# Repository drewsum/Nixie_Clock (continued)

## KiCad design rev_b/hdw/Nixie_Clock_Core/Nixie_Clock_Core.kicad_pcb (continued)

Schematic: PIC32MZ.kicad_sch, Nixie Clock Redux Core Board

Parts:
R1001, R1002: 10k; R_0603; Tolerance 1%; Digi-Key PN 541-10.0KHCT-ND
U1001: PIC32MZ2048EFG100_IPF; TQFP-100_14x14mm_Pitch0.5mm; Digi-Key PN PIC32MZ2048EFG100-I/PF-ND

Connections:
+3.3VA_MZ: U1001.30 (AVDD); also elsewhere on the board
Anode_0: U1001.25 (RB0/PGED1/AN0/RPB0); also elsewhere on the board
Anode_1: U1001.24 (RB1/PGEC1/AN1/RPB1); also elsewhere on the board
Anode_2: U1001.23 (RB2/AN2/C2INB/RPB2); also elsewhere on the board
Anode_3: U1001.22 (RB3/AN3/C2INA/RPB3); also elsewhere on the board
Anode_4: U1001.21 (RB4/AN4/C1INB); also elsewhere on the board
Anode_5: U1001.20 (RB5/AN45/C1INA/RPB5); also elsewhere on the board
Buzzer_Enable: U1001.68 (RD9/EBIA15/RPD9/PMCS2/PMA15); also elsewhere on the board
CPU_Trap_LED: U1001.94 (RE1/EBID1/PMD1); also elsewhere on the board
Cathode_0: U1001.32 (RB8/EBIA10/AN48/RPB8/PMA10); also elsewhere on the board
Cathode_1: U1001.33 (RB9/EBIA7/AN49/RPB9/PMA7); also elsewhere on the board
Cathode_2: U1001.34 (RB10/EBIA13/CVREFOUT/AN5/RPB10/PMA13); also elsewhere on the board
Cathode_3: U1001.35 (RB11/AN6/ERXERR/AETXERR); also elsewhere on the board
Cathode_4: U1001.41 (RB12/EBIA11/AN7/ERXD0/AECRS/PMA11); also elsewhere on the board
Cathode_5: U1001.42 (RB13/AN8/ERXD1/AECOL); also elsewhere on the board
Cathode_6: U1001.43 (RB14/EBIA1/AN9/ERXD2/AETXD3/RPB14/SCK3/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); also elsewhere on the board
Cathode_7: U1001.44 (RB15/EBIA0/AN10/ERXD3/AETXD2/RPB15/OCFB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); also elsewhere on the board
Cathode_8: U1001.19 (RE9/AN26/AERXD1/RPE9); also elsewhere on the board
Cathode_9: U1001.18 (RE8/AN25/AERXD0/RPE8); also elsewhere on the board
Cathode_DP: U1001.17 (RA0/TMS/EBIA16/AN24); also elsewhere on the board
Colon_0: U1001.100 (RE4/EBID4/AN18/PMD4); also elsewhere on the board
Colon_1: U1001.99 (RE3/EBID3/RPE3/PMD3); also elsewhere on the board
Colon_2: U1001.98 (RE2/EBID2/PMD2); also elsewhere on the board
Colon_3: U1001.97 (RG13/TRD0/SQID0); also elsewhere on the board
ETC_Hardstrap: U1001.40 (RF12/TDO/EBIA17/AN31/RPF12); also elsewhere on the board
Error_LED: U1001.2 (RA5/EBIA5/AN34/PMA5); also elsewhere on the board
GND: U1001.13 (VSS), U1001.36 (VSS), U1001.45 (VSS), U1001.52 (VBUS3V3), U1001.53 (VSS), U1001.63 (VSS), U1001.75 (VSS), U1001.84 (VSS), U1001.92 (VSS); also elsewhere on the board
GNDA_MZ: U1001.31 (AVSS); also elsewhere on the board
Heartbeat_LED: U1001.91 (RE0/EBID0/PMD0); also elsewhere on the board
I2C_SCL: R1002.2, U1001.65 (RF5/EBIA8/RPF5/SCL5/PMA8); also elsewhere on the board
I2C_SDA: R1001.2, U1001.64 (RF4/EBIA9/RPF4/SDA5/PMA9); also elsewhere on the board
PGOOD_LED_SHDN: U1001.96 (RG12/TRD1/SQID1); also elsewhere on the board
PIC32MZ_ICSPCLK: U1001.26 (RB6/PGEC2/AN46/RPB6); also elsewhere on the board
PIC32MZ_ICSPDAT: U1001.27 (RB7/PGED2/AN47/RPB7); also elsewhere on the board
PIC32MZ_POSC_EC: U1001.49 (RC12/OSC1/CLKI); also elsewhere on the board
PIC32MZ_REFCLK1: U1001.72 (RC13/SOSCI/RPC13); also elsewhere on the board
PIC32MZ_SOSC_EC: U1001.73 (RC14/SOSCO/RPC14/T1CK); also elsewhere on the board
POS3P3_PGOOD: U1001.87 (RG1/EBID9/ETXERR/RPG1/PMD9); also elsewhere on the board
POS24_PGOOD: U1001.88 (RG0/EBID8/RPG0/PMD8); also elsewhere on the board
POS90_ADC: U1001.9 (RC4/~EBIOE/AN19/RPC4/PMRD); also elsewhere on the board
POS90_PGOOD: U1001.38 (RA1/TCK/EBIA19/AN29); also elsewhere on the board
POS180_ADC: U1001.8 (RC3/~EBIWE/AN20/RPC3/PMWR); also elsewhere on the board
POS180_PGOOD: U1001.29 (RA10/VREF+/CVREF+/AN28/AERXD3); also elsewhere on the board
POS180_RUN: U1001.28 (RA9/VREF-/CVREF-/AN27/AERXD2); also elsewhere on the board
Pushbutton_0: U1001.71 (RD0/EMDIO/AEMDIO/RPD0/RTCC/INT0); also elsewhere on the board
Pushbutton_1: U1001.76 (RD1/RPD1/SCK1); also elsewhere on the board
Pushbutton_2: U1001.77 (RD2/EBID14/ETXEN/RPD2/PMD14); also elsewhere on the board
Pushbutton_3: U1001.78 (RD3/EBID15/ETXCLK/RPD3/PMD15); also elsewhere on the board
Pushbutton_4: U1001.79 (RD12/EBID12/ETXD2/RPD12/PMD12); also elsewhere on the board
Pushbutton_5: U1001.80 (RD13/EBID13/ETXD3/PMD13); also elsewhere on the board
Pushbutton_6: U1001.81 (RD4/~SQICS0/RPD4); also elsewhere on the board
RTC_Hardstrap: U1001.39 (RF13/TDI/EBIA18/AN30/RPF13/SCK5); also elsewhere on the board
Reset_LED: U1001.1 (RG15/AN23/AERXERR); also elsewhere on the board
Telemetry_Hardstrap: U1001.58 (RF8/EBIRDY2/RPF8/SCL3); also elsewhere on the board
USB_UART_RX: U1001.85 (RF0/EBID11/ETXD1/RPF0/PMD11); also elsewhere on the board
USB_UART_TX: U1001.86 (RF1/EBID10/ETXD0/RPF1/PMD10); also elsewhere on the board
VBAT_ADC: U1001.7 (RC2/EBIA12/AN21/RPC2/PMA12); also elsewhere on the board
VBAT_PGOOD: U1001.48 (RD15/AN33/AETXD1/RPD15/SCK6); also elsewhere on the board
~Display_Detect: U1001.82 (RD5/~SQICS1/RPD5); also elsewhere on the board
~IO_Level_Shift_Enable: U1001.90 (RA7/TRD3/SQID3); also elsewhere on the board
~PIC32MZ_MCLR: U1001.15 (~MCLR); also elsewhere on the board

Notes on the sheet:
POSC
OC1
U3RX
U3TX
AN20
ICSP2DAT
SDA5
REFCLKO1
AN19
ICSP2CLK
SCL5
SOSC
AN21

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
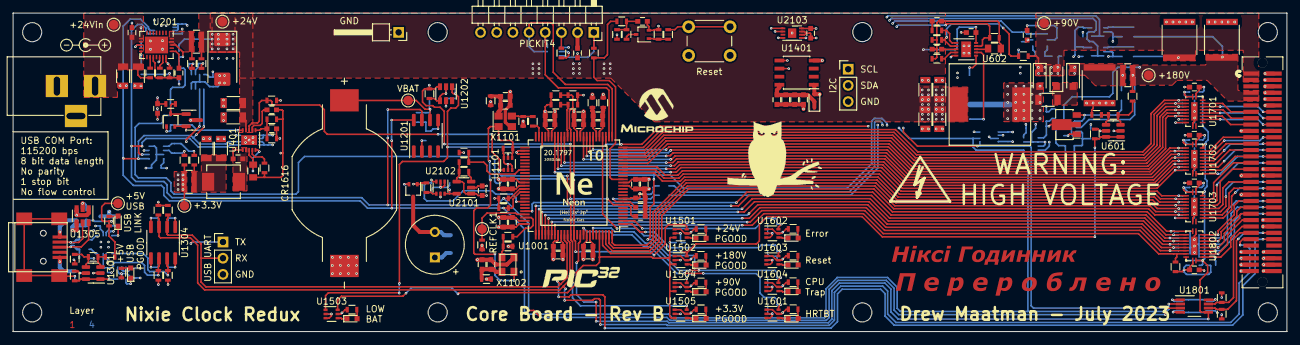
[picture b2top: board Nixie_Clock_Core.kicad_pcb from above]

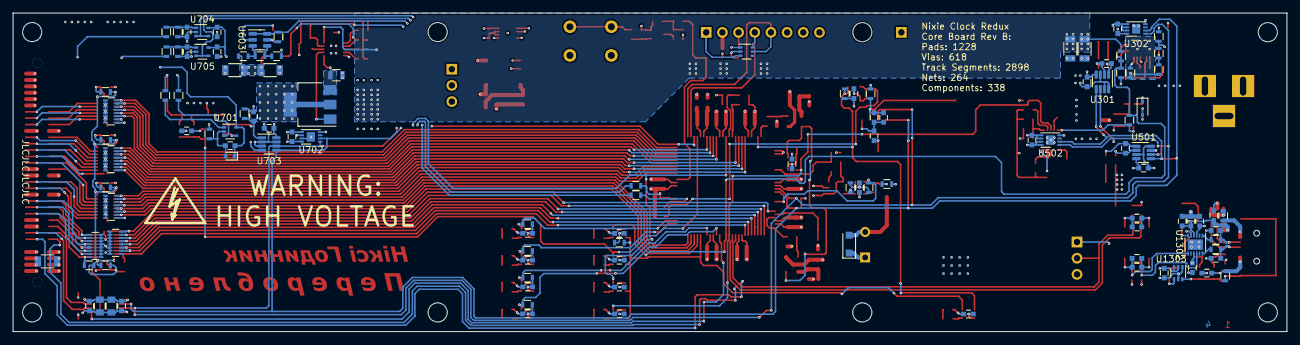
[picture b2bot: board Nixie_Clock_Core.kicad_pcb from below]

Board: 4 copper layers, 200.0 x 50.0 mm, 330 parts (115 on the bottom side), 201 nets.

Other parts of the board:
TP601, TP602: TP; Test_Point

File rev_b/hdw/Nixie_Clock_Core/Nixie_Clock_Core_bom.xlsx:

References | Value | Configuration | Footprint | Quantity | Digi-Key PN
BT1201 | CR1616 | BACKUP_RTC |  | 1 | P034-ND
BT1202 | CR1616_Holder | BACKUP_RTC | BAT_BU1632SM-JJ-GTR | 1 | BU1632SM-JJ-GCT-ND
BZ2101 | CST-931RP-A |  | MagneticBuzzer_CUI_CST-931RP-A | 1 | 102-1461-ND
C409 C1308 C1309 | 47pF |  | C_0603 | 3 | 13-CC0603JPNPO9BN470CT-ND
C203 C404 C607 | 10nF |  | C_0603 | 3 | 1276-1009-1-ND
C204 C406 C604 C605 C610 C614 C801 C802 C901 C902 C905 C906 C909 C910 C913 C914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 | 0.1uF |  | C_0603 | 44 | 1276-1935-1-ND
C1201 C1203 C1204 C1205 | 0.1uF | BACKUP_RTC | C_0603 | 4 | 1276-1935-1-ND
C1404 | 0.1uF | ETC | C_0603 | 1 | 1276-1935-1-ND
C609 C611 C612 | 0.1uF |  | C_1206 | 3 | 399-C1206C104K2RECAUTOCT-ND
C613 C1901 C1902 | 1.5uF |  | C_2220 | 3 | 565-4697-1-ND
C402 C608 C1803 C1805 | 4.7uF |  | C_0805 | 4 | 1276-2970-1-ND
C405 C903 C904 C907 C908 C911 C912 C915 C916 C1104 C1105 C1304 C1311 C1313 | 10uF |  | C_0603 | 14 | 1276-1871-1-ND
C1202 | 10uF | BACKUP_RTC | C_0603 | 1 | 1276-1871-1-ND
C1401 C1402 C1403 | 10uF | ETC | C_0603 | 3 | 1276-1871-1-ND
C201 C202 C205 C206 C401 C403 C407 C408 C601 C602 C603 C606 C1903 | 10uF |  | C_1206 | 13 | 1276-6767-1-ND
C207 | 47uF |  | CP_EIA-7343-43_Kemet-X | 1 | 399-16639-1-ND
D1401 | BAT48JFILM | ETC | D_SOD-323 | 1 | 497-5711-1-ND
D401 | BAT48JFILM |  | D_SOD-323 | 1 | 497-5711-1-ND
D1302 D1501 D1502 D1504 D1505 D1601 | Green |  | LED_0603 | 6 | 754-1121-1-ND
D801 | PESD3V3L5UY |  | SOT-363_SC-70-6 | 1 | 1727-3828-1-ND
D1503 D1602 D1603 D1604 | Red |  | LED_0603 | 4 | 754-1117-1-ND
D601 D602 D603 D2101 | SMD1200PL |  | D_SOD-123F | 4 | SMD1200PL-TPMSCT-ND
D1301 | Yellow |  | LED_0603 | 1 | 754-1124-1-ND
J1901 | Conn_02x32_Top_Bottom |  | CONN_5120527-1_TYC | 1 | A97407CT-ND
J1301 | USB_B_Mini |  | USB_Mini-B | 1 | 732-2109-1-ND
L401 | 2.2uH |  | L_Vishay_IHLP-2020 | 1 | 541-1268-1-ND
L601 | 680uH |  | Wurth_7447709681 | 1 | 732-1700-1-ND
L801 L802 L901 L902 L1101 L1102 L1301 L1302 | 600R 0.5A |  | L_0603 | 8 | 490-1014-1-ND
N201 | 24V PSU |  |  | 1 | 1939-1835-ND
Q401 Q801 Q2101 | BSS214NW |  | SOT-323_SC-70 | 3 | BSS214NWH6327XTSA1CT-ND
Q601 | IRFL214 |  | SOT-223-3_TabPin2 | 1 | IRFL214PBFCT-ND
Q402 | ZXMS6004FFTA |  | SOT-23 | 1 | ZXMS6004FFCT-ND
R206 R406 | 0.02 |  | R_0612 | 2 | P16010CT-ND
R611 | 0.36 |  | R_0805 | 1 | RL12S.36FCT-ND
R616 | 1.5 |  | R_0612 | 1 | RCL06121R20FKEA
R401 R801 R803 R1103 R1104 R2110 | 10 |  | R_0603 | 6 | 541-10.0HCT-ND
R2106 | 10 | ETC | R_0603 | 1 | 541-10.0HCT-ND
R2109 | 10 | BACKUP_RTC | R_0603 | 1 | 541-10.0HCT-ND
R1308 R1309 | 27 |  | R_0603 | 2 | 541-5306-1-ND
R602 | 330 |  | R_0603 | 1 | 541-330HCT-ND
R805 R1301 R1310 R1502 R1503 R1504 R1505 R1506 R1603 R1604 R1607 R1608 | 1k |  | R_0603 | 12 | 541-1.00KHCT-ND
R609 | 1.33k |  | R_0603 | 1 | 541-1.33KHCT-ND
R211 | 1.6k |  | R_0603 | 1 | 541-5237-1-ND
R201 | 1.78k |  | R_0603 | 1 | 541-1.78KHCT-ND
R603 | 3.4k |  | R_0603 | 1 | 541-3.40KHCT-ND
R1303 | 6.04k |  | R_0603 | 1 | 541-CRCW06036K04FKEBCT-ND
R610 | 6.49k |  | R_0603 | 1 | 541-5537-1-ND
R203 R204 R207 R210 R212 R402 R404 R605 R612 R802 R804 R1001 R1002 R1101 R1102 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 | 10k |  | R_0603 | 38 | 541-10.0KHCT-ND
R606 | 10k |  | R_0603 | 1 | 541-10.0KHCT-ND
R604 | 14k |  | R_0603 | 1 | 541-CRCW060314K0FKTACT-ND
R403 | 18.2k |  | R_0603 | 1 | 541-18.2KHCT-ND
R614 | 28.7k |  | R_0603 | 1 | 541-28.7KHCT-ND
R1304 | 40.2k |  | R_0603 | 1 | 541-5412-1-ND
R607 R1306 R1307 R1311 R1312 | 100k |  | R_0603 | 5 | 541-100KHCT-ND
R202 | 200k |  | R_0603 | 1 | 541-4027-1-ND
R1202 | 220k | BACKUP_RTC | R_0603 | 1 | 541-4039-1-ND
R409 | 309k |  | R_0603 | 1 | 541-309KHCT-ND
R1302 | 487k |  | R_0603 | 1 | 541-487KHCT-ND
R1201 | 1M | BACKUP_RTC | R_0603 | 1 | 541-1.00MHCT-ND
R408 | 1M |  | R_0603 | 1 | 541-1.00MHCT-ND
R2101 | 1.07M |  | R_0603 | 1 | 541-1.07MHCT-ND
R601 | 1.6M |  | R_0603 | 1 | 541-1.60MHCT-ND
R608 R613 | 1.6M |  | R_0603 | 2 | 541-1.60MHCT-ND
RN1701 RN1702 RN1703 RN1801 RN1802 | 10k |  | R_Array_Convex_8x0602 | 5 | Y1103CT-ND
U1101 | 74LVC1G97 |  | SOT-363_SC-70-6 | 1 | 296-15582-1-ND
U1303 U1601 U1602 U1603 U1604 | 74LVC1G97 |  | SOT-363_SC-70-6 | 5 | 296-15582-1-ND
U1501 U1502 U1504 U1505 | 74LVC1G97 |  | SOT-363_SC-70-6 | 4 | 296-15582-1-ND
U1503 | 74LVC1G97 |  | SOT-363_SC-70-6 | 1 | 296-15582-1-ND
U2102 | 74LVC1G97 |  | SOT-363_SC-70-6 | 1 | 296-15582-1-ND
U1701 U1702 U1703 U1802 | 74VHC541 |  | WQFN-20-1EP_2.5x4.5mm_P0.5mm_EP1x2.9mm | 4 | 1727-7068-1-ND
U1401 | DS1683 | ETC | SOIC-8_3.9x4.9mm_Pitch1.27mm | 1 | DS1683S+-ND
U1201 | DS3231MZ | BACKUP_RTC | SOIC-8_3.9x4.9mm_P1.27mm | 1 | DS3231MZ+-ND
U1302 | FT234XD |  | DFN-12-1EP_3x3mm_Pitch0.45mm | 1 | 768-1178-1-ND
U1304 | ISO7321C |  | SOIC-8_3.9x4.9mm_P1.27mm | 1 | 296-42102-1-ND
U602 | LT3757 |  | DFN-10-1EP_3x3mm_Pitch0.5mm | 1 | LT3757IDD#PBF
U401 | LT8609A-DD |  | DFN-10-1EP_3x3mm_Pitch0.5mm | 1 | 505-LT8609AEDDM#TRPBFCT-ND
U2101 | LTC6900 |  | SOT-23-5 | 1 | LTC6900CS5#TRMPBFCT-ND
U1001 | PIC32MZ2048EFG100_IPF |  | TQFP-100_14x14mm_Pitch0.5mm | 1 | PIC32MZ0512EFE100-I/PF-ND
U1801 | TCA9803 |  | VSSOP-8_3.0x3.0mm_P0.65mm | 1 | 296-47829-1-ND
U1202 | TLV6700 | BACKUP_RTC | SOT-23-6 | 1 | 296-51696-1-ND
U601 U603 U1301 | TLV6700 |  | SOT-23-6 | 3 | 296-51696-1-ND
U1305 | TPD3S014DBVR |  | SOT-23-6 | 1 | 296-38835-1-ND
U201 | TPS26600RHFT |  | QFN-24-1EP_4x5mm_Pitch0.5mm | 1 | 296-45478-1-ND
X1101 | ASE-8.000MHz |  | Oscillator_SMD_Abracon_ASE-4Pin_3.2x2.5mm | 1 | 535-9558-1-ND
X1102 | ECS-327KE |  | ECS-327KE | 1 | XC1751CT-ND

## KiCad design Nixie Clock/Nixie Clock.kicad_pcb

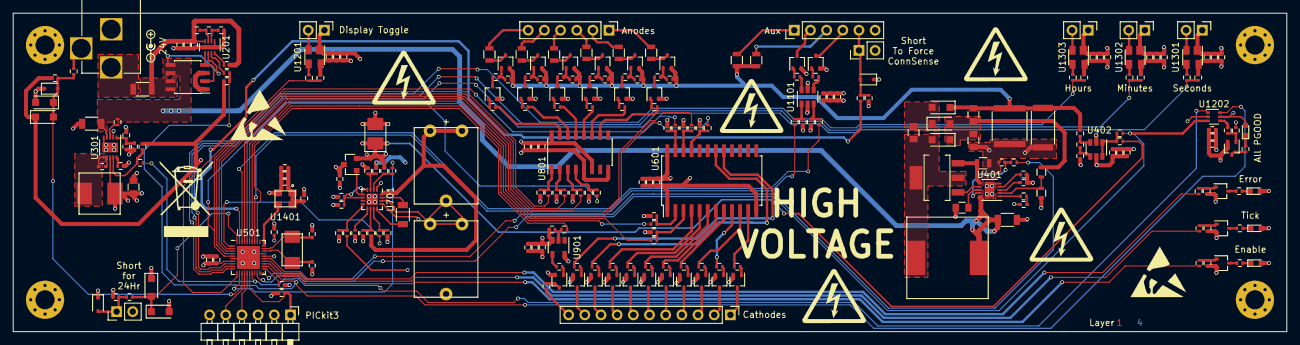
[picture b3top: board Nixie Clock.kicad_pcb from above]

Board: 4 copper layers, 200.0 x 50.0 mm, 267 parts (0 on the bottom side), 195 nets.

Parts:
C201, C406, C409, C501, C601, C801, C901, C1101, C1201, C1204, C1301, C1304, C1307, C1401: 0.1uF; C_0402
C202, C410, C502, C602, C802, C902, C1102, C1202, C1205, C1302, C1305, C1308, C1402: 10nF; C_0402
C203, C411, C503, C603, C803, C903, C1103, C1203, C1206, C1303, C1306, C1309, C1403: 1nF; C_0402
C301: 0.47uF; C_0402
C302: 4.7uF; C_1206
C303: 22uF; C_0805
C304: 15pF; C_0402
C401, C402, C404: 0.1uF; C_0805
C403: 2.2uF; C_2220
C405: 10uF; C_1206
C407: 4.7uF; C_0805
C408: 6.8nF; C_0402
C504, C505: 12pF; C_0402
C701: 100uF; CP_Tantalum_Case-B_EIA-3528-21_Reflow
C702: 2.2uF; C_0402
C703: 2.2uF; C_1206
C704, C705: 15F; MAL219691214E3
D201, D202, D401, D402, D403, D1204, D1205: SMD1200PL; D_SOD-123F
D203, D1206, D1501: 3.3V; D_SOD-323
D1201: PGOOD; LED_0603
D1202: Error; LED_0603
D1203: Tick; LED_0603
D1207: Enable; LED_0603
DTM_Logo_Small: DTM_Logo_Small; DTM_Logo_Small_Flipped
F201: 3A; R_1206
J201: Power Input; BARREL_JACK
J501: PicKit3_Header; Pin_Header_Angled_1x06_Pitch2.54mm
J1201: Display; Pin_Header_Straight_1x02_Pitch2.54mm
J1301: Seconds; Pin_Header_Straight_1x02_Pitch2.54mm
J1302: Minutes; Pin_Header_Straight_1x02_Pitch2.54mm
J1303: Hours; Pin_Header_Straight_1x02_Pitch2.54mm
J1501: Cathodes; Socket_Strip_Straight_1x11_Pitch2.54mm
J1502: Anodes; Socket_Strip_Straight_1x06_Pitch2.54mm
J1503: Aux; Socket_Strip_Straight_1x06_Pitch2.54mm
JP1201: 12Hr; Pin_Header_Straight_1x02_Pitch2.54mm
JP1501: ForceConnSense; Pin_Header_Straight_1x02_Pitch2.54mm
L301: 10uH; IHLP-2525CZ-01
L401: 680uH; Wurth_7447709681
L1401: BKP1005HS121-T; R_0402
Q201: Si4946; SOIC-8_3.9x4.9mm_Pitch1.27mm
Q401: IRFL214; SOT-223_3
Q701: DMP3099L; SOT-23
Q901, Q902, Q903, Q904, Q905, Q906, Q907, Q908, Q909, Q910, Q911, Q1003, Q1004, Q1007, Q1008, Q1011, Q1012, Q1101, Q1102: MMSTA42; SOT-323_SC-70
Q1001, Q1002, Q1005, Q1006, Q1009, Q1010: MMSTA92; SOT-323_SC-70
Q1201, Q1202, Q1203, Q1204: DMG1012UW; SOT-323_SC-70
R201, R1001, R1002, R1009, R1010, R1017, R1018, R1102, R1105, R1203, R1208, R1209, R1214: 100k; R_0402
R202, R207, R301, R304, R409, R502, R706, R707: 1M; R_0402
R203, R305: 1.3M; R_0402
R204, R208, R302, R402, R413, R602, R603, R604, R605, R606, R708, R710, R802, R803, R804, R805, R904, R1101, R1104, R1202, R1207, R1302, R1304, R1306, R1504: 100; R_0402
R205: 4.64k; R_0402
R206: 25.5k; R_0402
R303: 2.2M; R_0402
R306: 115k; R_0402
R401: 27k; R_2512
R403, R501, R601, R607, R608, R609, R610, R712, R801, R806, R807, R808, R903, R908, R1005, R1006, R1013, R1014, R1021, R1022, R1103, R1106, R1201, R1205, R1206, R1212, R1213, R1216, R1301, R1303, R1305, R1501: 10k; R_0402
R404: 0.16; R_0805
R405: 1.5M; R_0603
R406: 14k; R_0402
R407: 27k; R_0603
R408: 22k; R_0402
R410: 1.6M; R_0402
R411: 330; R_0402
R412: 3.3k; R_0402
R701: 1.96M; R_0402
R702: 255k; R_0402
R703, R711: 1.21M; R_0402
R704: 80.6k; R_0402
R705: 0; R_0402
R709: 3.83M; R_0402
R713: 536k; R_0402
R901, R902, R906, R907, R909, R910, R911, R912, R913, R914: 20k; R_0402
R905: 33k; R_0402
R1003, R1004, R1011, R1012, R1019, R1020: 470k; R_0402
R1007, R1008, R1015, R1016, R1023, R1024: 22k; R_0805
R1204, R1210, R1211, R1215: 10; R_0402
R1502, R1503: 200k; R_0805
U201: LTC4365IDDB; DFN-8-1EP_2x3mm_Pitch0.5mm
U301: LT3973-DD; DFN-10-1EP_3x3mm_Pitch0.5mm
U401: LT3757; DFN-10-1EP_3x3mm_Pitch0.5mm
U402: LT6700-1-S6; SOT-23-6
U501: PIC16LF1519-I/MV; QFN-40-1EP_5x5mm_Pitch0.4mm
U601: 74HC4514; SOIC-24W_7.5x15.4mm_Pitch1.27mm
U701: LTC3226; QFN-16-1EP_3x3mm_Pitch0.5mm
U801: 74HC238; SOIC-16_3.9x9.9mm_Pitch1.27mm
U901: 74AUC1G17; SOT-23-5
U1101: 74LVC2G17; SOT-23-6
U1201, U1301, U1302, U1303: MAX6816; SOT-143
U1202: 74LVC1G11; SOT-363_SC-70-6
U1401: ECS-327KE
Y501: 20MHz; CX5032GB20000H0PESZZ

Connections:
24hr: D1204.2, D1205.1, R1207.2, U501.40
+3V3: C303.1, C304.1, C409.1, C410.1, C411.1, C601.1, C602.1, C603.1, C702.1, C801.1, C802.1, C803.1, C901.1, C902.1, C903.1, C1101.1, C1102.1, C1103.1, C1201.1, C1202.1, C1203.1, C1204.1, C1205.1, C1206.1, C1301.1, C1302.1, C1303.1, C1304.1, C1305.1, C1306.1, C1307.1, C1308.1, C1309.1, D1201.2, D1202.2, D1203.2, D1204.1, D1207.2, L301.2, Q701.3, R303.1, R601.1, R701.1, R705.1, R801.1, R1201.1, R1206.1, R1301.1, R1303.1, R1305.1, R1501.1, U301.2, U301.8, U402.5, U601.24, U701.13, U801.6, U801.16, U901.5, U1101.5, U1201.4, U1202.5, U1301.4, U1302.4, U1303.4
/Backup Supply/BCKUP_EN_CHG: R705.2, R712.1, U701.8
/Backup Supply/BCKUP_PROG: R713.1, U701.9
/Backup Supply/C+: C703.1, U701.15
/Backup Supply/C-: C703.2, U701.12
/Backup Supply/CAPGOODR: R707.2, R710.1, U701.11
/Backup Supply/CPO: C704.1, R709.1, U701.16
/Backup Supply/CPO_FB: R709.2, R711.1, U701.10
/Backup Supply/LDO_FB: R702.2, R704.1, U701.4, U701.6
/Backup Supply/PFI: R701.2, R703.1, U701.3
/Backup Supply/VMID: C704.2, C705.1, U701.14
/Backup Supply/~PFOR: R706.2, R708.1, U701.2
/Connectors/colon0R: J1503.1, R1503.2
/Connectors/colon1R: J1503.3, R1502.2
/Controller Supply/3P3_BOOST: C301.1, U301.7
/Controller Supply/3P3_FB: C304.2, R303.2, R305.1, U301.1
/Controller Supply/3P3_PGOODR: R301.2, R302.2, U301.9
/Controller Supply/3P3_RT: R306.1, U301.10
/Controller Supply/3P3_RUN: R304.2, U301.3
/Controller Supply/3P3_SW: C301.2, L301.1, U301.6
/Display Supply/VVVINA: R410.2, R411.1, U402.3
/Display Supply/VVVINB: R411.2, R412.1, U402.4
/Display Supply/VVV_CS: Q401.3, R404.1, U401.6
/Display Supply/VVV_FBX: R405.2, R407.1, U401.2
/Display Supply/VVV_GATE: Q401.1, U401.7
/Display Supply/VVV_RT: R406.1, U401.4
/Display Supply/VVV_RUN_R: R402.2, R403.1, U401.9
/Display Supply/VVV_SS: C406.1, U401.3
/Display Supply/VVV_SW1: C401.2, D403.2, L401.2, Q401.2, Q401.4
/Display Supply/VVV_SW2: C402.2, C404.1, D402.2, D403.1, R405.1
/Display Supply/VVV_SW3: C401.1, D401.2, D402.1
/External Oscillator/VDD_OSC: C1401.1, C1402.1, C1403.1, L1401.2, U1401.1, U1401.4
/Highside Decoder/BCOA_R: R802.1, R808.1, U801.1
/Highside Decoder/BCOB_R: R803.1, R807.1, U801.2
/Highside Decoder/BCOC_R: R804.1, R806.1, U801.3
/Highside Decoder/BCOEN_R: R801.2, R805.1, U801.4
/Input/Output/ALL_PGOOD: R1204.1, U1202.4
/Lowside Decoder/BCDA_R: R603.1, R610.1, U601.2
/Lowside Decoder/BCDB_R: R604.1, R609.1, U601.3
/Lowside Decoder/BCDC_R: R605.1, R608.1, U601.21
/Lowside Decoder/BCDD_R: R606.1, R607.1, U601.22
/Lowside Decoder/BCDEN_R: R601.2, R602.1, U601.23
/Power Input/PlugSense: J201.3, R208.1
/Power Input/Vin_Gate: Q201.2, Q201.4, U201.5
/Power Input/Vin_OV: R205.2, R206.1, U201.2
/Power Input/Vin_SHDN: R201.2, U201.8
/Power Input/Vin_Source: Q201.1, Q201.3
/Power Input/Vin_UV: R203.2, R205.1, U201.3
/Power Input/Vin_Unfused: F201.1, J201.1
BCDA: R603.2, U501.34
BCDB: R604.2, U501.35
BCDC: R605.2, U501.36
BCDD: R606.2, U501.37
BCOA: R804.2, U501.2
BCOB: R803.2, U501.3
BCOC: R802.2, U501.4
ColonDrive0: R1101.2, U501.33
ColonDrive1: R1104.2, U501.38
EXT_OSC: U501.30, U1401.3
EnableInd: R1215.1, U501.23
ErrorInd: R1210.1, U501.25
GND: C201.2, C202.2, C203.2, C302.2, C303.2, C403.2, C404.2, C405.2, C406.2, C407.2, C408.2, C409.2, C410.2, C411.2, C501.2, C502.2, C503.2, C504.2, C505.2, C601.2, C602.2, C603.2, C701.2, C702.2, C705.2, C801.2, C802.2, C803.2, C901.2, C902.2, C903.2, C1101.2, C1102.2, C1103.2, C1201.2, C1202.2, C1203.2, C1204.2, C1205.2, C1206.2, C1301.2, C1302.2, C1303.2, C1304.2, C1305.2, C1306.2, C1307.2, C1308.2, C1309.2, C1401.2, C1402.2, C1403.2, D202.2, D203.1, D1205.2, D1206.1, D1501.1, J201.2, J501.3, J1201.1, J1301.1, J1302.1, J1303.1, J1503.6, JP1201.2, JP1501.2, Q901.2, Q902.2, Q903.2, Q904.2, Q905.2, Q906.2, Q907.2, Q908.2, Q909.2, Q910.2, Q911.2, Q1003.2, Q1004.2, Q1007.2, Q1008.2, Q1011.2, Q1012.2, Q1101.2, Q1102.2, Q1201.2, Q1202.2, Q1203.2, Q1204.2, R206.2, R305.2, R306.2, R401.2, R403.2, R404.2, R406.2, R407.2, R412.2, R501.2, R607.2, R608.2, R609.2, R610.2, R703.2, R704.2, R711.2, R712.2, R713.2, R806.2, R807.2, R808.2, R908.2, R1103.2, R1106.2, R1205.2, R1212.2, R1213.2, R1216.2, U201.1, U201.9, U301.5, U301.11, U401.5, U401.11, U402.2, U501.6, U501.27, U501.41, U601.1, U601.12, U701.17, U801.5, U801.8, U901.3, U1101.2, U1201.1, U1202.2, U1301.1, U1302.1, U1303.1, U1401.2
HighSideBase0: R1005.1, U801.15
HighSideBase1: R1006.1, U801.14
HighSideBase2: R1013.1, U801.13
HighSideBase3: R1014.1, U801.12
HighSideBase4: R1021.1, U801.11
HighSideBase5: R1022.1, U801.10
ICSPCLK: J501.5, U501.14
ICSPDAT: J501.4, U501.15
LowSideBase0: R901.1, U601.11
LowSideBase1: R902.1, U601.9
LowSideBase2: R906.1, U601.10
LowSideBase3: R907.1, U601.8
LowSideBase4: R909.1, U601.7
LowSideBase5: R910.1, U601.6
LowSideBase6: R911.1, U601.5
LowSideBase7: R912.1, U601.4
LowSideBase8: R913.1, U601.18
LowSideBase9: R914.1, U601.17
LowSideBaseDec: R904.2, U501.32
unnamed: C407.1, U401.8
unnamed: C408.1, R408.2
unnamed: D1201.1, R1203.1
unnamed: D1202.1, R1208.1
unnamed: D1203.1, R1209.1
unnamed: D1206.2, JP1201.1, R1206.2, R1207.1
unnamed: D1207.1, R1214.1
unnamed: D1501.2, J1503.5, JP1501.1, R1501.2, R1504.2
unnamed: J1201.2, U1201.2
unnamed: J1301.2, U1301.2
unnamed: J1302.2, U1302.2
unnamed: J1303.2, U1303.2
unnamed: Q701.1, U701.5
unnamed: Q901.1, R901.2
unnamed: Q902.1, R902.2
unnamed: Q903.1, R905.2
unnamed: Q903.3, R903.2
unnamed: Q904.1, R906.2
unnamed: Q905.1, R907.2
unnamed: Q906.1, R909.2
unnamed: Q907.1, R910.2
unnamed: Q908.1, R911.2
unnamed: Q909.1, R912.2
unnamed: Q910.1, R913.2
unnamed: Q911.1, R914.2
unnamed: Q1001.1, R1001.1, R1003.2
unnamed: Q1001.3, R1007.2
unnamed: Q1002.1, R1002.1, R1004.2
unnamed: Q1002.3, R1008.2
unnamed: Q1003.1, R1005.2
unnamed: Q1003.3, R1003.1
unnamed: Q1004.1, R1006.2
unnamed: Q1004.3, R1004.1
unnamed: Q1005.1, R1009.1, R1011.2
unnamed: Q1005.3, R1015.2
unnamed: Q1006.1, R1010.1, R1012.2
unnamed: Q1006.3, R1016.2
unnamed: Q1007.1, R1013.2
unnamed: Q1007.3, R1011.1
unnamed: Q1008.1, R1014.2
unnamed: Q1008.3, R1012.1
unnamed: Q1009.1, R1017.1, R1019.2
unnamed: Q1009.3, R1023.2
unnamed: Q1010.1, R1018.1, R1020.2
unnamed: Q1010.3, R1024.2
unnamed: Q1011.1, R1021.2
unnamed: Q1011.3, R1019.1
unnamed: Q1012.1, R1022.2
unnamed: Q1012.3, R1020.1
unnamed: Q1101.1, R1102.2
unnamed: Q1102.1, R1105.2
unnamed: Q1201.1, R1204.2, R1205.1
unnamed: Q1201.3, R1203.2
unnamed: Q1202.1, R1210.2, R1212.1
unnamed: Q1202.3, R1208.2
unnamed: Q1203.1, R1211.2, R1213.1
unnamed: Q1203.3, R1209.2
unnamed: Q1204.1, R1215.2, R1216.1
unnamed: Q1204.3, R1214.2
unnamed: R204.1, U201.7
unnamed: R408.1, U401.1
unnamed: R409.2, R413.1, U402.1, U402.6
unnamed: R501.1, U501.21
unnamed: R904.1, R908.1, U901.2
unnamed: R905.1, U901.4
unnamed: R1101.1, R1103.1, U1101.1
unnamed: R1102.1, U1101.6
unnamed: R1104.1, R1106.1, U1101.3
unnamed: R1105.1, U1101.4
unnamed: R1202.1, U1201.3
unnamed: R1302.1, U1301.3
unnamed: R1304.1, U1302.3
unnamed: R1306.1, U1303.3
OSC1: C505.1, U501.28, Y501.2
OSC2: C504.1, U501.29, Y501.1
PLUG: D201.2, D202.1, D203.2, R207.2, R208.2, U501.13
TickInd: R1211.1, U501.24
VCC_BCKUP: C501.1, C502.1, C503.1, C701.1, D201.1, J501.2, L1401.1, Q701.2, R202.1, R207.1, R301.1, R409.1, R502.1, R702.1, R706.1, R707.1, U501.7, U501.26, U701.1
VCC_BCKUP_PGOOD: R710.2, U501.1
VCC_PGOOD: R302.1, U501.17, U1202.1
VCOM: C302.1, C405.1, L401.1, Q201.5, Q201.6, R304.1, U201.6, U301.4, U401.10
VCOM_PGOOD: R202.2, R204.2, U501.22, U1202.6
VVV_PGOOD: R413.2, U501.19, U1202.3
VVV_RUN: R402.1, U501.20
Vin: C201.1, C202.1, C203.1, F201.2, Q201.7, Q201.8, R201.1, R203.1, U201.4
Vvv: C402.1, C403.1, D401.1, Q1001.2, Q1002.2, Q1005.2, Q1006.2, Q1009.2, Q1010.2, R401.1, R410.1, R1001.2, R1002.2, R1009.2, R1010.2, R1017.2, R1018.2, R1502.1, R1503.1
anode0: J1502.6, R1007.1
anode1: J1502.5, R1008.1
anode2: J1502.4, R1015.1
anode3: J1502.3, R1016.1
anode4: J1502.2, R1023.1
anode5: J1502.1, R1024.1
cathode0: J1501.1, Q901.3
cathode1: J1501.2, Q902.3
cathode2: J1501.3, Q904.3
cathode3: J1501.4, Q905.3
cathode4: J1501.5, Q906.3
cathode5: J1501.6, Q907.3
cathode6: J1501.7, Q908.3
cathode7: J1501.8, Q909.3
cathode8: J1501.9, Q910.3
cathode9: J1501.10, Q911.3
cathodeDec: J1501.11, R903.1
colon0: J1503.2, Q1101.3
colon1: J1503.4, Q1102.3
~ConnSense: R1504.1, U501.39
~DSPLY_TGL: R1201.2, R1202.2, U501.11
~DecodeEN: R602.2, R805.2, U501.5
~MCLR: J501.1, R502.2, U501.16
~SetHours: R1305.2, R1306.2, U501.10
~SetMinutes: R1303.2, R1304.2, U501.9
~SetSeconds: R1301.2, R1302.2, U501.8
~VCC_BCKUP_PFO: R708.2, U501.12

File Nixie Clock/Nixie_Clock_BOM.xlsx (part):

Nixie Clock REV A Bill of Materials
Id | Designator | Package | Quantity | Designation | Supplier | Supplier Part Num | Price | Extended Price | Total
1 | C201,C406,C409,C501,C601,C801,C901,C1101,C1201,C1204,C1301,C1304,C1307,C1401 | C_0402 | 14 | 0.1uF | Digi-Key | 587-1456-1-ND | 0.1 | 1.4000000000000001 | 114.62999999999998
2 | C202,C410,C502,C602,C802,C902,C1102,C1202,C1205,C1302,C1305,C1308,C1402 | C_0402 | 13 | 10nF | Digi-Key | 490-4762-1-ND | 0.1 | 1.3
3 | C203,C411,C503,C603,C803,C903,C1103,C1203,C1206,C1303,C1306,C1309,C1403 | C_0402 | 13 | 1nF | Digi-Key | 311-1036-1-ND | 0.1 | 1.3
4 | C301 | C_0402 | 1 | 0.47uF | Digi-Key | 587-3810-1-ND | 0.21 | 0.21
5 | C302 | C_1206 | 1 | 4.7uF | Digi-Key | 587-3368-1-ND | 0.49 | 0.49
6 | C303 | C_0805 | 1 | 22uF | Digi-Key | 587-1958-1-ND | 0.45 | 0.45
7 | C304 | C_0402 | 1 | 15pF | Digi-Key | 311-1017-1-ND | 0.1 | 0.1
8 | C401,C402,C404 | C_0805 | 3 | 0.1uF | Digi-Key | 399-3486-1-ND | 0.28999999999999998 | 0.86999999999999988
9 | C403 | C_2220 | 1 | 1.5uF | Digi-Key | 565-4697-1-ND | 1.97 | 1.97
10 | C405 | C_1206 | 1 | 10uF | Digi-Key | 587-2484-1-ND | 0.35 | 0.35
11 | C407 | C_0805 | 1 | 4.7uF | Digi-Key | 587-1297-1-ND | 0.2 | 0.2
12 | C408 | C_0402 | 1 | 6.8nF | Digi-Key | 311-1726-1-ND | 0.1 | 0.1
13 | C504,C505 | C_0402 | 2 | 12pF | Digi-Key | 399-1013-1-ND | 0.1 | 0.2
14 | C701 | CP_Tantalum_Case-B_EIA-3528-21_Reflow | 1 | 100uF | Digi-Key | 478-8198-1-ND | 1.05 | 1.05
15 | C702 | C_0402 | 1 | 2.2uF | Digi-Key | 587-1453-1-ND | 0.19 | 0.19
16 | C703 | C_1206 | 1 | 2.2uF | Digi-Key | 490-1815-1-ND | 0.31 | 0.31
17 | C704,C705 | MAL219691214E3 | 2 | 15F | Digi-Key | 4706PHBK-ND | 9.3800000000000008 | 18.760000000000002
18 | D201,D202,D401,D402,D403,D1204,D1205 | D_SOD-123F | 7 | SMD1200PL | Digi-Key | SMD1200PL-TPMSCT-ND | 0.49 | 3.4299999999999997
19 | D203,D1206,D1501 | D_SOD-323 | 3 | 3.3V | Digi-Key | 1727-4152-1-ND | 0.39 | 1.17
20 | D1201 | LED_0603 | 1 | PGOOD | Digi-Key | 160-1446-1-ND | 0.28999999999999998 | 0.28999999999999998
21 | D1202 | LED_0603 | 1 | Error | Digi-Key | 160-1447-1-ND | 0.28999999999999998 | 0.28999999999999998
22 | D1203 | LED_0603 | 1 | Tick | Digi-Key | 160-1448-1-ND | 0.31 | 0.31
23 | D1207 | LED_0603 | 1 | Enable | Digi-Key | 160-1446-1-ND | 0.28999999999999998 | 0.28999999999999998
24 | F201 | R_1206 | 1 | 3A | Digi-Key | 507-1082-1-ND | 0.33 | 0.33
25 | J201 | BARREL_JACK | 1 | Power Input | Digi-Key | CP-002A-ND | 0.6 | 0.6
26 | J501 | Pin_Header_Angled_1x06_Pitch2.54mm | 1 | PicKit3_Header | On Hand |  |  | 0
27 | J1201 | Pin_Header_Straight_1x02_Pitch2.54mm | 1 | Display | On Hand |  |  | 0
28 | J1301 | Pin_Header_Straight_1x02_Pitch2.54mm | 1 | Seconds | On Hand |  |  | 0
29 | J1302 | Pin_Header_Straight_1x02_Pitch2.54mm | 1 | Minutes | On Hand |  |  | 0
30 | J1303 | Pin_Header_Straight_1x02_Pitch2.54mm | 1 | Hours | On Hand |  |  | 0
31 | J1501 | Socket_Strip_Straight_1x11_Pitch2.54mm | 1 | Cathodes | On Hand |  |  | 0
32 | J1502 | Socket_Strip_Straight_1x06_Pitch2.54mm | 1 | Anodes | On Hand |  |  | 0
33 | J1503 | Socket_Strip_Straight_1x06_Pitch2.54mm | 1 | Aux | On Hand |  |  | 0
34 | JP1201 | Pin_Header_Straight_1x02_Pitch2.54mm | 1 | 12Hr | On Hand |  |  | 0
35 | JP1501 | Pin_Header_Straight_1x02_Pitch2.54mm | 1 | ForceConnSense | On Hand |  |  | 0
36 | L301 | IHLP-2525CZ-01 | 1 | 10uH | Digi-Key | 541-1013-1-ND | 2.73 | 2.73
37 | L401 | Wurth_7447709681 | 1 | 680uH | Digi-Key | 732-1700-1-ND | 2.41 | 2.41
38 | L1401 | R_0402 | 1 | BKP1005HS121-T | Digi-Key | 587-1921-1-ND | 0.1 | 0.1
39 | Q201 | SOIC-8_3.9x4.9mm_Pitch1.27mm | 1 | Si4946 | Digi-Key | SI4946BEY-T1-E3CT-ND | 1.19 | 1.19
40 | Q401 | SOT-223_3 | 1 | IRFL214 | Digi-Key | IRFL214PBFCT-ND | 1.07 | 1.07
41 | Q701 | SOT-23 | 1 | DMP3099L | Digi-Key | DMP3099L-7DICT-ND | 0.37 | 0.37
42 | Q901,Q902,Q903,Q904,Q905,Q906,Q907,Q908,Q909,Q910,Q911,Q1003,Q1004,Q1007,Q1008,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 | SOT-323_SC-70 | 19 | MMSTA42 | Digi-Key | MMSTA42TPMSCT-ND | 0.3 | 5.7
43 | Q1001,Q1002,Q1005,Q1006,Q1009,Q1010 | SOT-323_SC-70 | 6 | MMSTA92 | Digi-Key | MMSTA92-TPCT-ND | 0.42 | 2.52
44 | Q1201,Q1202,Q1203,Q1204 | SOT-323_SC-70 | 4 | DMG1012UW | Digi-Key | DMG1012UW-7DICT-ND | 0.37 | 1.48
 | R1203,R1208,R1209,R1214 | R_0402 | 4 | 1k | Digi-Key | 311-1.0KJRCT-ND | 0.1 | 0.4
45 | R201,R1001,R1002,R1009,R1010,R1017,R1018,R1102,R1105 | R_0402 | 9 | 100k | Digi-Key | 311-100KLRCT-ND | 0.1 | 0.9
46 | R202,R207,R301,R304,R409,R502,R706,R707 | R_0402 | 8 | 1M | Digi-Key | 311-1.00MLRCT-ND | 0.1 | 0.8
47 | R203,R305 | R_0402 | 2 | 1.3M | Digi-Key | YAG3283CT-ND | 0.1 | 0.2
48 | R204,R208,R302,R402,R413,R602,R603,R604,R605,R606,R708,R710,R802,R803,R804,R805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 | R_0402 | 25 | 100 | Digi-Key | 311-100LRCT-ND | 0.1 | 2.5
49 | R205 | R_0402 | 1 | 4.64k | Digi-Key | 311-4.64KLRCT-ND | 0.1 | 0.1
50 | R206 | R_0402 | 1 | 25.5k | Digi-Key | YAG3076CT-ND | 0.1 | 0.1
51 | R303 | R_0402 | 1 | 2.2M | Digi-Key | YAG3292CT-ND | 0.1 | 0.1
52 | R306 | R_0402 | 1 | 115k | Digi-Key | YAG2956CT-ND | 0.1 | 0.1
53 | R401 | R_2512 | 1 | 27k | Digi-Key | A116066CT-ND | 0.67 | 0.67
54 | R403,R501,R601,R607,R608,R609,R610,R712,R801,R806,R807,R808,R903,R908,R1005,R10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 | R_0402 | 32 | 10k | Digi-Key | 311-10.0KLRCT-ND | 0.1 | 3.2
55 | R404 | R_0805 | 1 | 0.16 | Digi-Key | 311-.16SCT-ND | 0.42 | 0.42
56 | R405 | R_0603 | 1 | 1.5M | Digi-Key | 311-1.50MHRCT-ND | 0.1 | 0.1
57 | R406 | R_0402 | 1 | 14k | Digi-Key | 311-14.0KLRCT-ND | 0.1 | 0.1
58 | R407 | R_0603 | 1 | 27k | Digi-Key | 311-27.0KHRCT-ND | 0.1 | 0.1
59 | R408 | R_0402 | 1 | 22k | Digi-Key | 311-22.0KLRCT-ND | 0.1 | 0.1
60 | R410 | R_0402 | 1 | 1.6M | Digi-Key | YAG3284CT-ND | 0.1 | 0.1
61 | R411 | R_0402 | 1 | 330 | Digi-Key | 311-330LRCT-ND | 0.1 | 0.1
62 | R412 | R_0402 | 1 | 3.4k | Digi-Key | YAG3149CT-ND | 0.1 | 0.1
63 | R701 | R_0402 | 1 | 1.96M | Digi-Key | 541-1.96MLCT-ND | 0.1 | 0.1
64 | R702 | R_0402 | 1 | 255k | Digi-Key | YAG3074CT-ND | 0.1 | 0.1
65 | R703,R711 | R_0402 | 2 | 1.21M | Digi-Key | RMCF0402FT1M21CT-ND | 0.1 | 0.2
66 | R704 | R_0402 | 1 | 80.6k | Digi-Key | 311-80.6KLRCT-ND | 0.1 | 0.1
67 | R705 | R_0402 | 1 | 0 | Digi-Key | 311-0.0JRCT-ND | 0.1 | 0.1
68 | R709 | R_0402 | 1 | 3.83M | Digi-Key | 541-3.83MLCT-ND | 0.1 | 0.1
69 | R713 | R_0402 | 1 | 536k | Digi-Key | YAG3181CT-ND | 0.1 | 0.1
70 | R901,R902,R906,R907,R909,R910,R911,R912,R913,R914 | R_0402 | 10 | 20k | Digi-Key | 311-2.20KLRCT-ND | 0.1 | 1
71 | R905 | R_0402 | 1 | 33k | Digi-Key | YAG2970CT-ND | 0.1 | 0.1
72 | R1003,R1004,R1011,R1012,R1019,R1020 | R_0402 | 6 | 470k | Digi-Key | 311-470KLRCT-ND | 0.1 | 0.60000000000000009
73 | R1007,R1008,R1015,R1016,R1023,R1024 | R_0805 | 6 | 18k | Digi-Key | 311-18KARCT-ND | 0.1 | 0.60000000000000009
74 | R1204,R1210,R1211,R1215 | R_0402 | 4 | 10 | Digi-Key | 311-10.0LRCT-ND | 0.1 | 0.4
75 | R1502,R1503 | R_0805 | 2 | 200k | Digi-Key | 311-200KCRCT-ND | 0.1 | 0.2
76 | U201 | DFN-8-1EP_2x3mm_Pitch0.5mm | 1 | LTC4365IDDB | Digi-Key | LTC4365IDDB#TRMPBFCT-ND | 4.0199999999999996 | 4.0199999999999996
77 | U301 | DFN-10-1EP_3x3mm_Pitch0.5mm | 1 | LT3973-DD | Digi-Key | LT3973EDD#PBF-ND | 5.88 | 5.88
78 | U401 | DFN-10-1EP_3x3mm_Pitch0.5mm | 1 | LT3757 | Digi-Key | LT3757IDD#PBF-ND | 4.72 | 4.72
79 | U402 | SOT-23-6 | 1 | LT6700-1-S6 | Digi-Key | LT6700CS6-1#TRMPBFCT-ND | 3.07 | 3.07
80 | U501 | QFN-40-1EP_5x5mm_Pitch0.4mm | 1 | PIC16LF1519-I/MV | Digi-Key | PIC16LF1519-I/MV-ND | 1.95 | 1.95
81 | U601 | SOIC-24W_7.5x15.4mm_Pitch1.27mm | 1 | 74HC4514 | Digi-Key | 1727-6338-1-ND | 1.1599999999999999 | 1.1599999999999999
82 | U701 | QFN-16-1EP_3x3mm_Pitch0.5mm | 1 | LTC3226 | Digi-Key | LTC3226IUD#PBF-ND | 6.56 | 6.56
83 | U801 | SOIC-16_3.9x9.9mm_Pitch1.27mm | 1 | 74HC238 | Digi-Key | 74HC238D(BJ)CT-ND | 0.41 | 0.41
84 | U901 | SOT-23-5 | 1 | 74AUC1G17 | Digi-Key | 296-12654-1-ND | 0.48 | 0.48
85 | U1101 | SOT-23-6 | 1 | 74LVC2G17 | Digi-Key | 296-13012-1-ND | 0.54 | 0.54
86 | U1201,U1301,U1302,U1303 | SOT-143 | 4 | MAX6816 | Digi-Key | MAX6816EUS+TCT-ND | 3.41 | 13.64
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
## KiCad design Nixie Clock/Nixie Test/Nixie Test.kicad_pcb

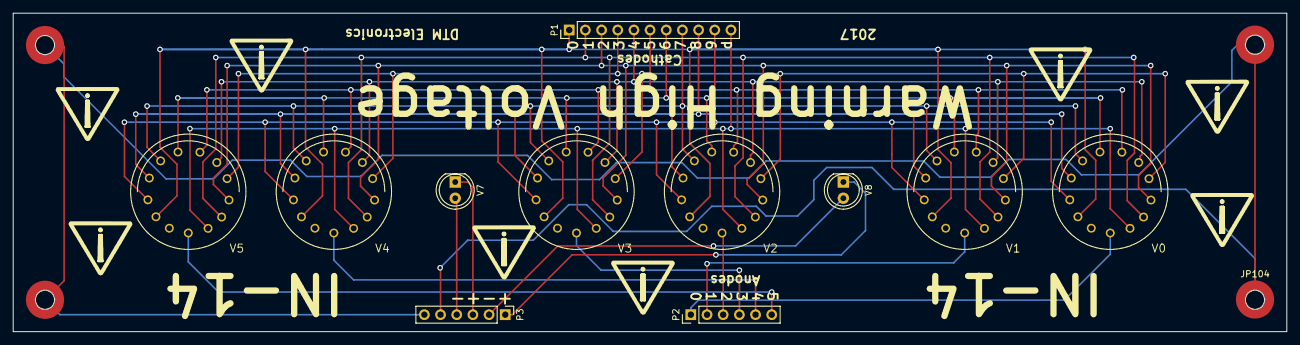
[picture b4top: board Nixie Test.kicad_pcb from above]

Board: 2 copper layers, 200.0 x 50.0 mm, 15 parts (0 on the bottom side), 26 nets.

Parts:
JP101, JP102, JP103, JP104: JUMPER; MountingHole_3mm_Pad_NPTH
P1: Cathodes; Pin_Header_Straight_1x11_Pitch2.54mm
P2: Anodes; Pin_Header_Straight_1x06_Pitch2.54mm
P3: Aux; Pin_Header_Straight_1x06_Pitch2.54mm
V0, V1, V2, V3, V4, V5: IN14; IN-14
V7, V8: IN3; LED_D5.0mm

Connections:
Anode0: P2.1, V0.1
Anode1: P2.2, V1.1
Anode2: P2.3, V2.1
Anode3: P2.4, V3.1
Anode4: P2.5, V4.1
Anode5: P2.6, V5.1
Cathode0: P1.1, V0.12, V1.12, V2.12, V3.12, V4.12, V5.12
Cathode1: P1.2, V0.3, V1.3, V2.3, V3.3, V4.3, V5.3
Cathode2: P1.3, V0.4, V1.4, V2.4, V3.4, V4.4, V5.4
Cathode3: P1.4, V0.5, V1.5, V2.5, V3.5, V4.5, V5.5
Cathode4: P1.5, V0.6, V1.6, V2.6, V3.6, V4.6, V5.6
Cathode5: P1.6, V0.7, V1.7, V2.7, V3.7, V4.7, V5.7
Cathode6: P1.7, V0.8, V1.8, V2.8, V3.8, V4.8, V5.8
Cathode7: P1.8, V0.9, V1.9, V2.9, V3.9, V4.9, V5.9
Cathode8: P1.9, V0.10, V1.10, V2.10, V3.10, V4.10, V5.10
Cathode9: P1.10, V0.11, V1.11, V2.11, V3.11, V4.11, V5.11
CathodeDec: P1.11, V0.2, V1.2, V2.2, V3.2, V4.2, V5.2
unnamed: JP101.1, JP102.1
unnamed: JP101.2, P3.6
unnamed: JP102.2, JP103.2
unnamed: JP103.1, JP104.1
unnamed: JP104.2, P3.5
colon0A: P3.1, V8.1
colon0C: P3.2, V8.2
colon1A: P3.3, V7.1
colon1C: P3.4, V7.2

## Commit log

2018-08-31 Initial commit of KiCad V4 project
2018-08-31 Added MPLAB project for U501 firmware
2021-02-22 added custom firmware for josh, doesn't blink colons every second
2023-05-13 broke off onto rev B
2023-05-14 lots of rev B control board schematic progress
2023-05-14 more rev b sch progress
2023-05-21 started IN-12B carrier board
2023-05-29 more carrier board progress
2023-06-03 revamped POS180 telemetry
2023-06-03 more schematic progress, assigning signals to MCU"
2023-06-03 updated footprints, ran some DRC
2023-06-10 hid all passive refdes on core PCB
2023-06-10 started grouping MCU components on PCB
2023-06-10 much more component placement on core board
2023-06-10 arranged USB components on PCB, added USB isolator Bypass
2023-06-10 much more core board component plcement
2023-06-10 annotated, started arranging parts for IN12 carrier
2023-06-11 more core board component placement
2023-06-25 chose new IO connector, fixed some net connectivity issues
2023-06-26 lots more PCB placement
2023-06-26 started PCB design rules, some layout
2023-07-03 lots of core board routing
2023-07-04 lots more core board routing
2023-07-07 routed all IO signals from buffers to PIC
2023-07-07 got to 0 unconnects
2023-07-07 dropped to four layers
2023-07-07 lots of placement progress on IN12 carrier board
2023-07-07 lots more IN12 carrier placement
2023-07-10 lots of routing and design progress on IN12 carrier board
2023-07-11 carrier board layout progress
2023-07-11 added cap touch sensors back
2023-07-12 all components within IN12 carrier board outline
2023-07-13 some misc signal routing on IN12 carrier
2023-07-14 more small signal routing on IN12 carrier
2023-07-15 got IN12 carrier board unconnects to 0
2023-07-19 added BOM for IN12 carrier, finished routing, some schematic tweaks, adjusted design rules for ERC
2023-07-21 lots of PCB improvements/touch ups
2023-07-28 fixed some core board ERC issues
2023-07-31 added BOM
2023-08-03 assigned digikey pns to IN12 carrier board parts
2023-08-12 generated gerbers
2023-08-14 created rev B PIC firmware project
2023-08-14 wrote pin macros, pulled in configuration.h
2023-08-14 imported lots of PIC32MZ EF fmw files
2023-08-14 wrote GPIO setup functions for all pins
2023-09-08 gitignore
2023-09-08 lots of firmware progress, got heartbeat working
2023-09-08 WDT working
2023-09-08 USB UART working
2023-09-08 some minor fixes
2023-09-09 ported prefetch and cause of reset
2023-09-09 updated MCU peripheral excel sheet, ported PMD code
2023-09-09 ported RTCC code, fixed some bugs with sscanf in format specifiers due to compiler update
2023-09-09 ported I2C master driver
2023-09-10 added some I2C device drivers
2023-09-23 first commit offirmware development with harmony
2023-09-23 added more harmony modules
2023-09-23 more harmony clowning, this doesnt work at all
2023-09-23 rev_b\sfw\
2023-09-23 rebuilt bare metal project
2023-09-23 ported some I2C telemetry stuff over
2023-09-24 ported lots of I2C stuff
2023-09-25 ported some ADC code, external channels not working very well
2023-09-25 fixed ADC channel mapping bug
2023-09-25 ported PGOOD monitoring
2023-09-25 added rough command to turn pos180 on and off
2023-10-01 started on some IN12 display carrier programming
2023-10-01 ported some LED driver code
2023-10-04 added display carrier SPD header file, added some more display board stuff
2023-10-12 added carrier SPD programming script, code to read SPD
2023-10-13 added ETC to IN-12 carrier code
2023-10-13 fixed typo in IN-12 ETC string
2023-10-15 got tube multiplexing code working
2023-10-22 got LED and ETC bit setting/clearing working on IN12 carrier board
2023-10-23 ported some clock state code, added code to set menu LEDs
2023-10-29 ported code to update IN12 display based on real clock functions
2023-10-29 Ported lots of clock functionality code. Brightness, etc
2023-10-29 added am_pm indication, alarm check code
2023-11-05 got pushbutton interrupts working
2023-11-11 added user5 layer to IN12 carrier layout for acrylic panel
2023-11-11 generated SVG
2023-11-25 added F360 project for case design
2023-11-25 added code for pushbutton handlers
2023-11-25 got power pushbutton working
2023-11-26 updated F360 project for case
2023-11-29 added CAD drawings for case walls
2023-11-30 fixed dimensions in top wall drawing
2023-12-01 updated laser cut to add 1/8th inch margin on all sides, LED holes, wider tube gaps
2023-12-03 updated CAD design to use 3D printed connector plate
2023-12-15 seem to be making progress on flickering bug
2023-12-15 more fruitless attempts at fixing flickering bug
2023-12-15 removed unneeded TMR register clearing
2023-12-15 fixed order of muxing callback functions
2023-12-16 got flicker resolved, using XC32 2.30
2023-12-16 got pushbuttons mostly working
2023-12-16 added code to set backlight color with pushbuttons
2023-12-16 fixed outdated code comment
2023-12-16 updated main.h
2023-12-16 added boot up ASCII art
2023-12-16 some more random enclosure odds and ends
2023-12-19 switched to snprintf buffer modification
2023-12-19 added random code for alarm and time format to USB UART
2023-12-20 added user manual
2023-12-20 fixed table of contents formatting
2023-12-20 some more user manual work
2023-12-21 updated user manual
2023-12-23 added some info about pushbuttons to user manual
2023-12-24 added much more to user manual
2023-12-25 regenerated production boms
2023-12-25 fixed some stuff in the IN12 BOM
2023-12-28 added clock overview section to users manual
2023-12-29 finished user manual
2024-01-03 fixed enclosure CAD drawings
2024-02-24 some bug fixes
2024-02-24 fixed bugs with setting AM/PM mode and alarm arm through pushbuttons
2024-02-24 slowed I2C baud rate to try to prevent LED driver bus hangs
2024-02-24 updated firmware revision to 0.95
